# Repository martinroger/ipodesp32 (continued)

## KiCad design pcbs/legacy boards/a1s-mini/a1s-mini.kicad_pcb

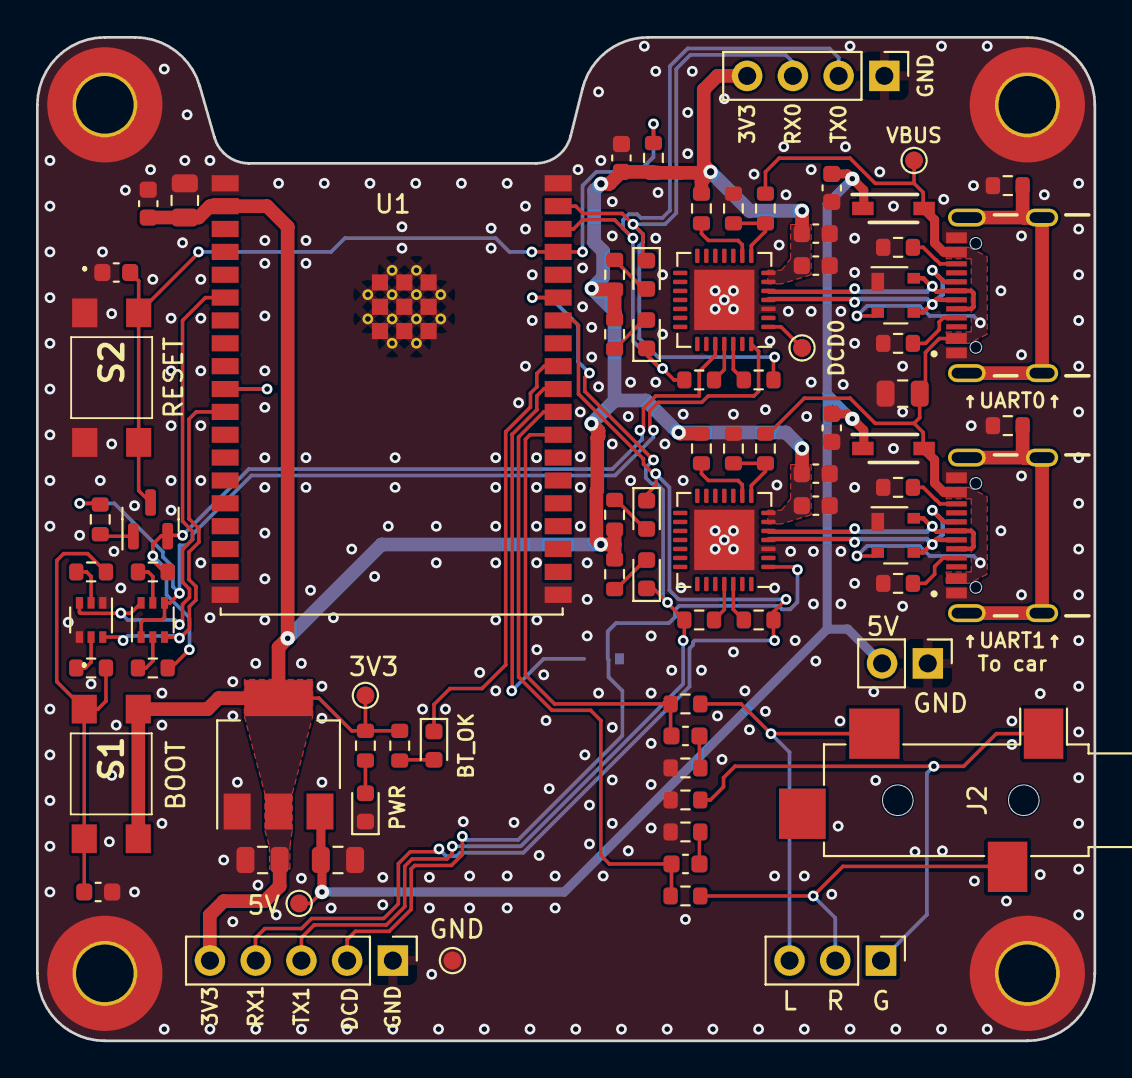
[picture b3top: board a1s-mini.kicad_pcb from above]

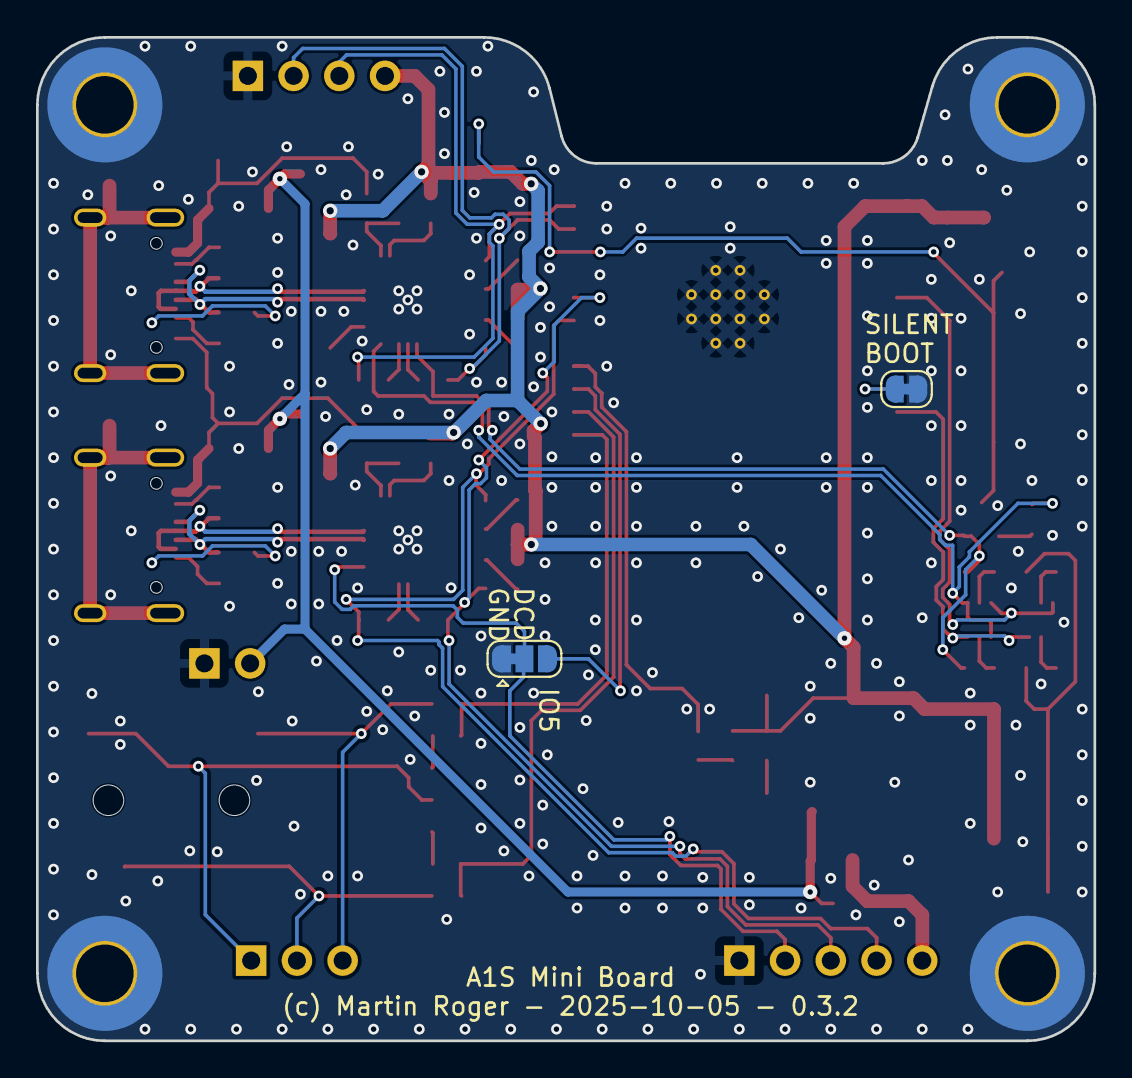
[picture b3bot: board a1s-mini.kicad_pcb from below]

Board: 2 copper layers, 58.8 x 55.7 mm, 86 parts (2 on the bottom side), 55 nets.

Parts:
3V1, 5V1: TestPoint_Small; TestPoint_Pad_D1.0mm
C1, C3, C4, C5, C8, C9, C11, C14: 0.1uF 50V; C_0603_1608Metric
C2, C6, C7, C16: 22uF 10V; C_0805_2012Metric
C10, C12, C13, C15: 10uF 10V; C_0603_1608Metric
D1, D2, D9, D11: 2.1V G 10mA; LED_0603_1608Metric
D5: 2.1V O 10mA; LED_0603_1608Metric
D6: 2V R 10mA; LED_0603_1608Metric
D7, D8: SP0503BAHTG; SOT-143
D10, D14: 1N5819HW-7-F; SOD3716X145N
DCD1: TestPoint_Small; TestPoint_Pad_D1.0mm
GND1: TestPoint_Small; TestPoint_Pad_D1.0mm
H1, H2, H3, H4: MountingHole_Pad; MountingHole_3.2mm_M3_Pad_TopBottom
J1: UART1; PinHeader_1x05_P2.54mm_Vertical
J2: SJ-3524-SMT-TR-PI; Jack_3.5mm_CUI_SJ-3524-SMT_Horizontal
J3: Audio Out; PinHeader_1x03_P2.54mm_Vertical
J4: UART0; PinHeader_1x04_P2.54mm_Vertical
J5, J6: USB4105-GF-A; GCT_USB4105-GF-A
J7: 5V; PinHeader_1x02_P2.54mm_Vertical
JP1: SolderJumper_3_Bridged12; SolderJumper-3_P1.3mm_Bridged12_RoundedPad1.0x1.5mm
JP2: SolderJumper_2_Bridged; SolderJumper-2_P1.3mm_Bridged_RoundedPad1.0x1.5mm
Q3: BC818; SOT-23
Q4, Q6: MBT3904DW1; SOT-363_SC-70-6
R1, R2, R5, R6, R34, R35: 1K 1%; R_0603_1608Metric
R7, R12, R13, R14, R32, R33: 10K 1%; R_0603_1608Metric
R8, R9: 22R 1%; R_0603_1608Metric
R10, R11, R18, R19, R21, R26, R27, R29, R31: 0R; R_0603_1608Metric
R15, R23: 22.1K 1%; R_0603_1608Metric
R16, R24: 47.5K 1%; R_0603_1608Metric
R17, R25: 2K 1%; R_0603_1608Metric
R20, R22, R28, R30: 5.1K 1%; R_0603_1608Metric
S1, S2: TL3305BF260QG
U1: ESP32 A1S; ESP32-A1S
U2: AZ1117CH-3.3TRG1; SOT-223-3_TabPin2
U3: CP2102N; QFN-28-1EP_5x5mm_P0.5mm_EP3.35x3.35mm
U4: CP2102-GM; QFN-28-1EP_5x5mm_P0.5mm_EP3.35x3.35mm
VBUS1: TestPoint_Small; TestPoint_Pad_D1.0mm

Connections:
+3.3V: 3V1.1, C1.2, C2.2, C3.2, C7.2, C10.2, C11.2, C13.2, C14.2, J1.5, J4.4, R1.1, R2.1, R5.1, R6.1, R7.1, R17.1, R25.1, R34.1, R35.1, S1.3, S1.4, U1.2 (3V3), U2.2 (VO), U3.6 (VDD), U3.7 (VREGIN), U4.6 (VDD), U4.7 (VREGIN)
+5V: 5V1.1, C6.2, C12.2, C15.2, D10.1, D14.1, J7.2, U2.3 (VI)
/CP2102N_0/D+: D7.3 (K), J5.A6 (DP1), J5.B6 (DP2), U3.4 (D+)
/CP2102N_0/D-: D7.4 (K), J5.A7 (DN1), J5.B7 (DN2), U3.5 (D-)
/CP2102N_0/DCD: DCD1.1, U3.1 (~DCD)
/CP2102_1/D+: D8.3 (K), J6.A6 (DP1), J6.B6 (DP2), U4.4 (D+)
/CP2102_1/D-: D8.4 (K), J6.A7 (DN1), J6.B7 (DN2), U4.5 (D-)
/CP2102_1/DCD: J1.2, JP1.2 (C), U4.1 (~DCD)
AGND: J2.S, J3.1, R31.1
DTR0: Q6.1 (E1), Q6.4 (E2), R12.1, U3.28 (~DTR)
EN: C8.2, Q3.3 (C), R7.2, S2.3, S2.4, U1.35 (EN)
GND: C1.1, C2.1, C3.1, C6.1, C7.1, C8.1, C9.1, C10.1, C11.1, C12.1, C13.1, C14.1, C15.1, C16.1, D5.1 (K), D7.1 (A), D8.1 (A), GND1.1, H1.1, H2.1, H3.1, H4.1, J1.1, J4.1, J5.A1_B12 (GND), J5.B1_A12 (GND__1), J6.A1_B12 (GND), J6.B1_A12 (GND__1), J7.1, JP1.1 (A), JP2.2 (B), Q4.1 (E1), Q4.4 (E2), R8.2, R9.2, R16.2, R20.1, R21.2, R22.2, R24.2, R28.1, R29.2, R30.2, R31.2, S2.1, S2.2, U1.1 (GND), U1.19 (GND), U1.20 (GND), U1.38 (GND), U1.39 (GND), U2.1 (GND), U3.3 (GND), U3.29 (GND), U4.3 (GND), U4.29 (GND)
HPOUTL: C4.2, R10.1, U1.27 (HPOUTL)
HPOUTR: C5.2, R11.1, U1.28 (HPOUTR)
IO0: Q4.3 (C2), Q6.6 (C1), U1.6 (IO0)
IO2: Q4.6 (C1), Q6.3 (C2), U1.11 (IO2)
IO5: JP1.3 (B), U1.29 (IO5)
IO18: D6.1 (K), U1.30 (IO18)
LOUT: J2.T, J3.3, R10.2
unnamed: C4.1, R8.1
unnamed: C5.1, R9.1
unnamed: C9.2, R32.1, R33.1, S1.1, S1.2
unnamed: D1.2 (A), R1.2
unnamed: D2.2 (A), R2.2
unnamed: D5.2 (A), R5.2
unnamed: D6.2 (A), R6.2
unnamed: D9.2 (A), R34.2
unnamed: D11.2 (A), R35.2
unnamed: J5.A5 (CC1), R20.2
unnamed: J5.B5 (CC2), R22.1
unnamed: J5.SH1 (SHELL_GND), J5.SH2 (SHELL_GND__1), J5.SH3 (SHELL_GND__2), J5.SH4 (SHELL_GND__3), R21.1
unnamed: J6.A5 (CC1), R28.2
unnamed: J6.B5 (CC2), R30.1
unnamed: J6.SH1 (SHELL_GND), J6.SH2 (SHELL_GND__1), J6.SH3 (SHELL_GND__2), J6.SH4 (SHELL_GND__3), R29.1
unnamed: JP2.1 (A), U1.10 (IO15)
unnamed: Q3.1 (B), R12.2
unnamed: Q4.2 (B1), R33.2
unnamed: Q4.5 (B2), R32.2
unnamed: Q6.2 (B1), R13.2
unnamed: Q6.5 (B2), R14.2
unnamed: R19.1, U3.25 (RXD)
unnamed: R18.1, U3.26 (TXD)
unnamed: R15.2, R16.1, U3.8 (VBUS)
unnamed: R17.2, U3.9 (~RST)
unnamed: R27.1, U4.25 (RXD)
unnamed: R26.1, U4.26 (TXD)
unnamed: R23.2, R24.1, U4.8 (VBUS)
unnamed: R25.2, U4.9 (~RST)
ROUT: J2.R, J3.2, R11.2
RTS0: Q3.2 (E), R13.1, R14.1, U3.24 (~RTS)
RXD0: D1.1 (K), J4.3, R18.2, U1.37 (RXD0)
RXD1: D9.1 (K), J1.4, R26.2, U1.32 (IO19)
TXD0: D2.1 (K), J4.2, R19.2, U1.36 (TXD0)
TXD1: D11.1 (K), J1.3, R27.2, U1.33 (IO22)
VBUS: C16.2, D7.2 (K), D8.2 (K), D10.2, D14.2, J5.A4_B9 (VBUS), J5.B4_A9 (VBUS__1), J6.A4_B9 (VBUS), J6.B4_A9 (VBUS__1), R15.1, R23.1, VBUS1.1

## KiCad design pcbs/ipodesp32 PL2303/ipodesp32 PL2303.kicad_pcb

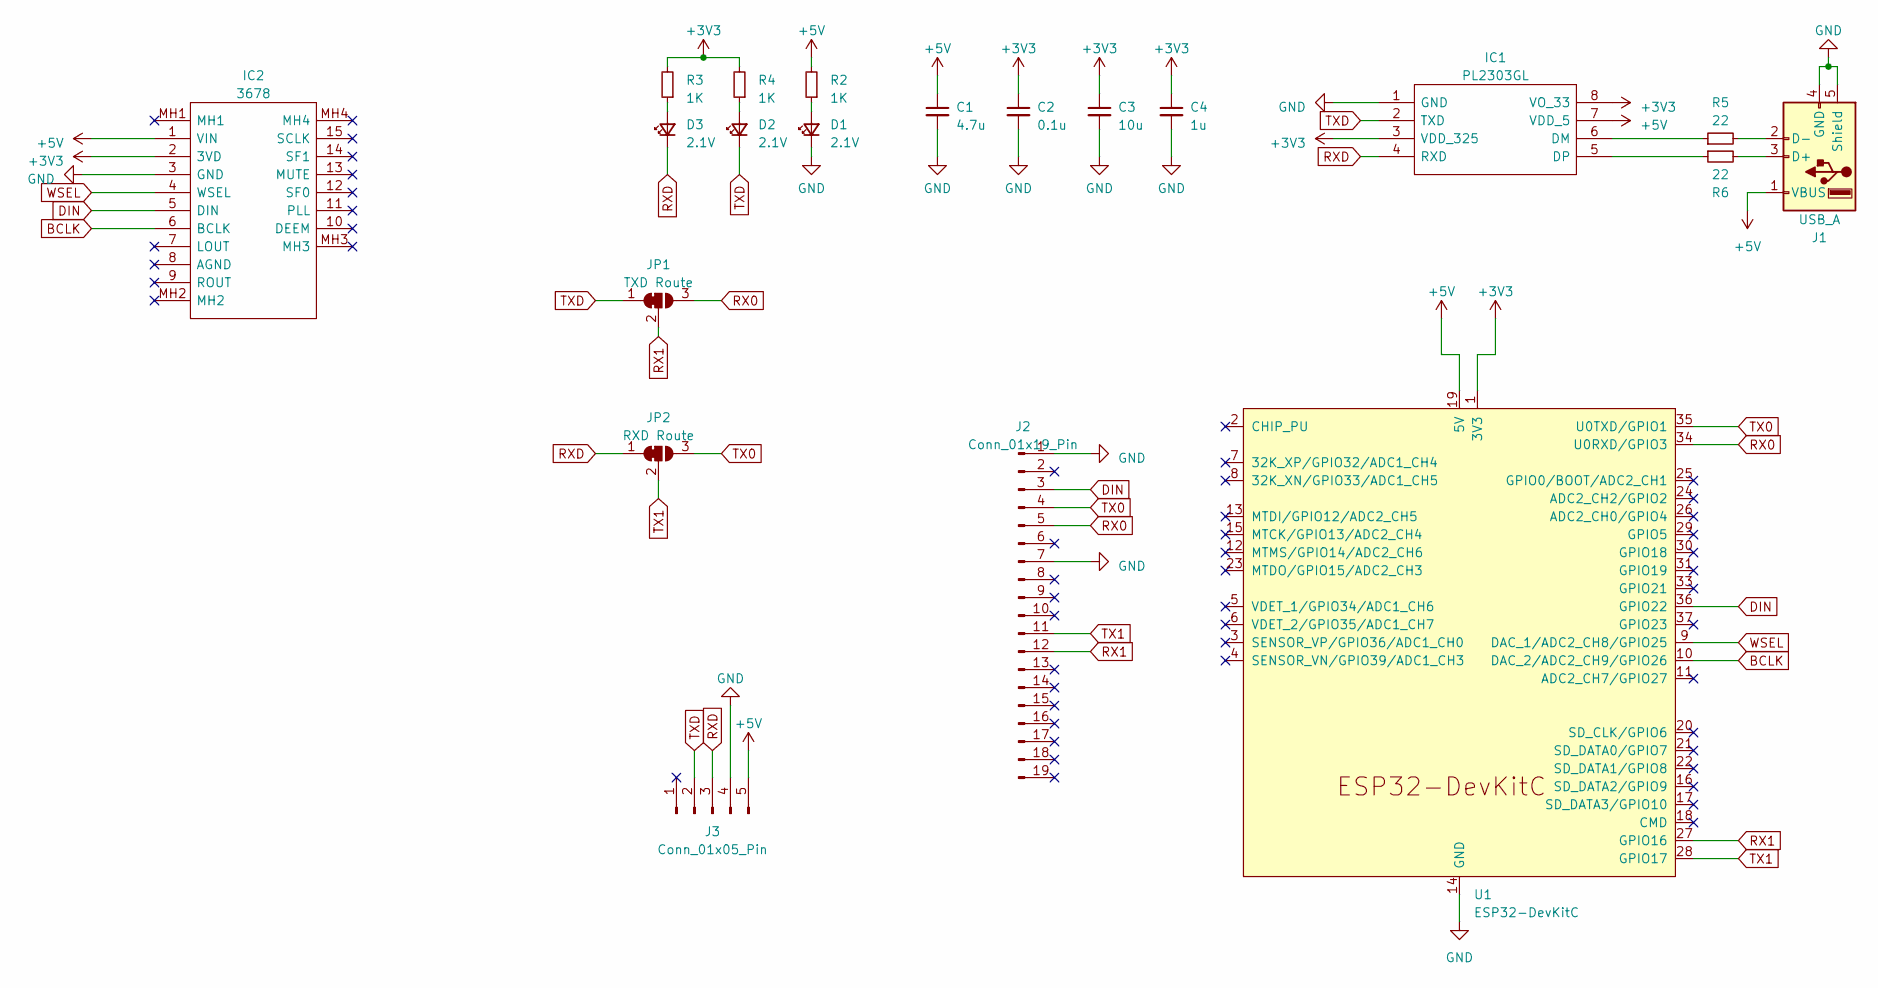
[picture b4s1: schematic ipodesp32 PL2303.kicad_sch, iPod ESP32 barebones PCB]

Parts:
C1: 4.7u; C_0603_1608Metric; Manufacturer_Part_Number CL10A475KP8NNNC
C2: 0.1u; C_0603_1608Metric; Manufacturer_Part_Number CC0603KRX7R7BB104
C3: 10u; C_0805_2012Metric; Manufacturer_Part_Number C0805C106K8PAC7800
C4: 1u; C_0603_1608Metric; Manufacturer_Part_Number CL10B105KP8NNNC
D1, D2, D3: 2.1V; LED_0603_1608Metric; Manufacturer_Part_Number LTST-C190GKT
IC1: PL2303GL; SOIC127P600X170-8N; Manufacturer_Part_Number PL2303GS
IC2: 3678; Manufacturer_Part_Number 3678
J1: USB_A; USB_A_CNCTech_1001-011-01101_Horizontal; Manufacturer_Part_Number 1001-011-01101
J2: Conn_01x19_Pin; PinHeader_1x19_P2.54mm_Vertical
J3: Conn_01x05_Pin; PinHeader_1x05_P2.54mm_Vertical
JP1: TXD Route; SolderJumper-3_P1.3mm_Bridged12_Pad1.0x1.5mm
JP2: RXD Route; SolderJumper-3_P1.3mm_Bridged12_Pad1.0x1.5mm
R2, R3, R4: 1K; R_0603_1608Metric; Manufacturer_Part_Number RC0603FR-071KL
R5, R6: 22; R_0603_1608Metric; Manufacturer_Part_Number RC0603FR-0722RL
U1: ESP32-DevKitC

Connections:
+3V3: C2.1, C3.1, C4.1, IC1.3 (VDD_325), IC1.8 (VO_33), IC2.2 (3VD), R3.2, R4.2, U1.1 (3V3)
+5V: C1.1, IC1.7 (VDD_5), IC2.1 (VIN), J1.1 (VBUS), J3.5, R2.2, U1.19 (5V)
BCLK: IC2.6 (BCLK), U1.10 (DAC_2/ADC2_CH9/GPIO26)
DIN: IC2.5 (DIN), J2.3, U1.36 (GPIO22)
GND: C1.2, C2.2, C3.2, C4.2, D1.1 (K), IC1.1 (GND), IC2.3 (GND), J1.4 (GND), J1.5 (Shield), J2.1, J2.7, J3.4, U1.14 (GND), U1.32 (GND), U1.38 (GND)
unnamed: D1.2 (A), R2.1
unnamed: D2.2 (A), R4.1
unnamed: D3.2 (A), R3.1
unnamed: IC1.6 (DM), R5.1
unnamed: IC1.5 (DP), R6.1
unnamed: J1.3 (D+), R6.2
unnamed: J1.2 (D-), R5.2
RX0: J2.5, JP1.3 (B), U1.34 (U0RXD/GPIO3)
RX1: J2.12, JP1.2 (C), U1.27 (GPIO16)
RXD: D3.1 (K), IC1.4 (RXD), J3.3, JP2.1 (A)
TX0: J2.4, JP2.3 (B), U1.35 (U0TXD/GPIO1)
TX1: J2.11, JP2.2 (C), U1.28 (GPIO17)
TXD: D2.1 (K), IC1.2 (TXD), J3.2, JP1.1 (A)
WSEL: IC2.4 (WSEL), U1.9 (DAC_1/ADC2_CH8/GPIO25)

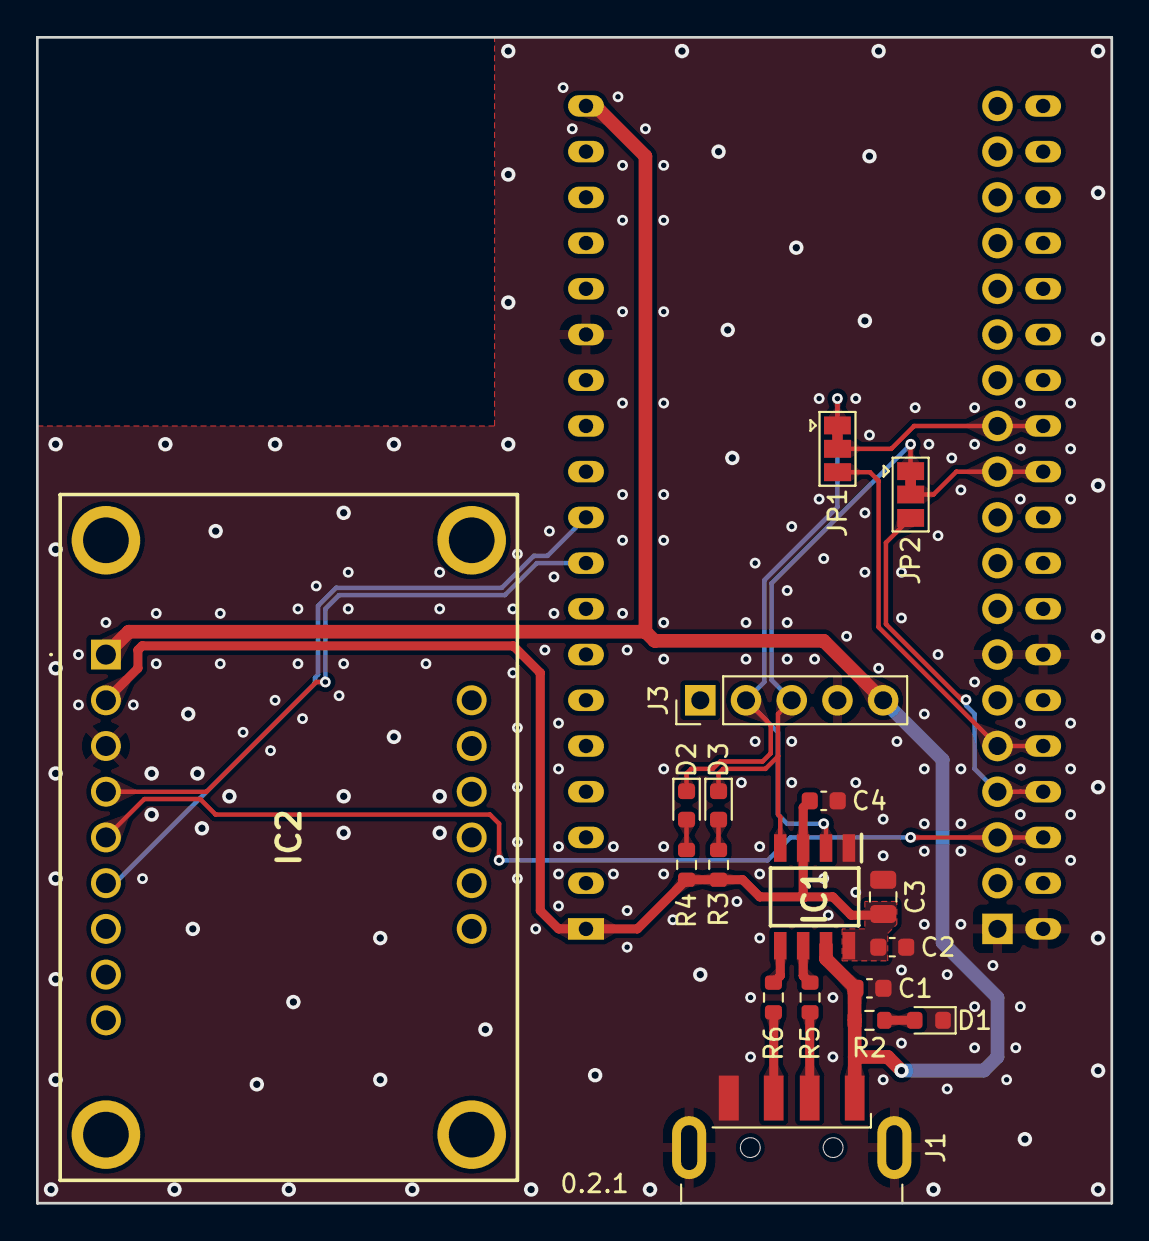
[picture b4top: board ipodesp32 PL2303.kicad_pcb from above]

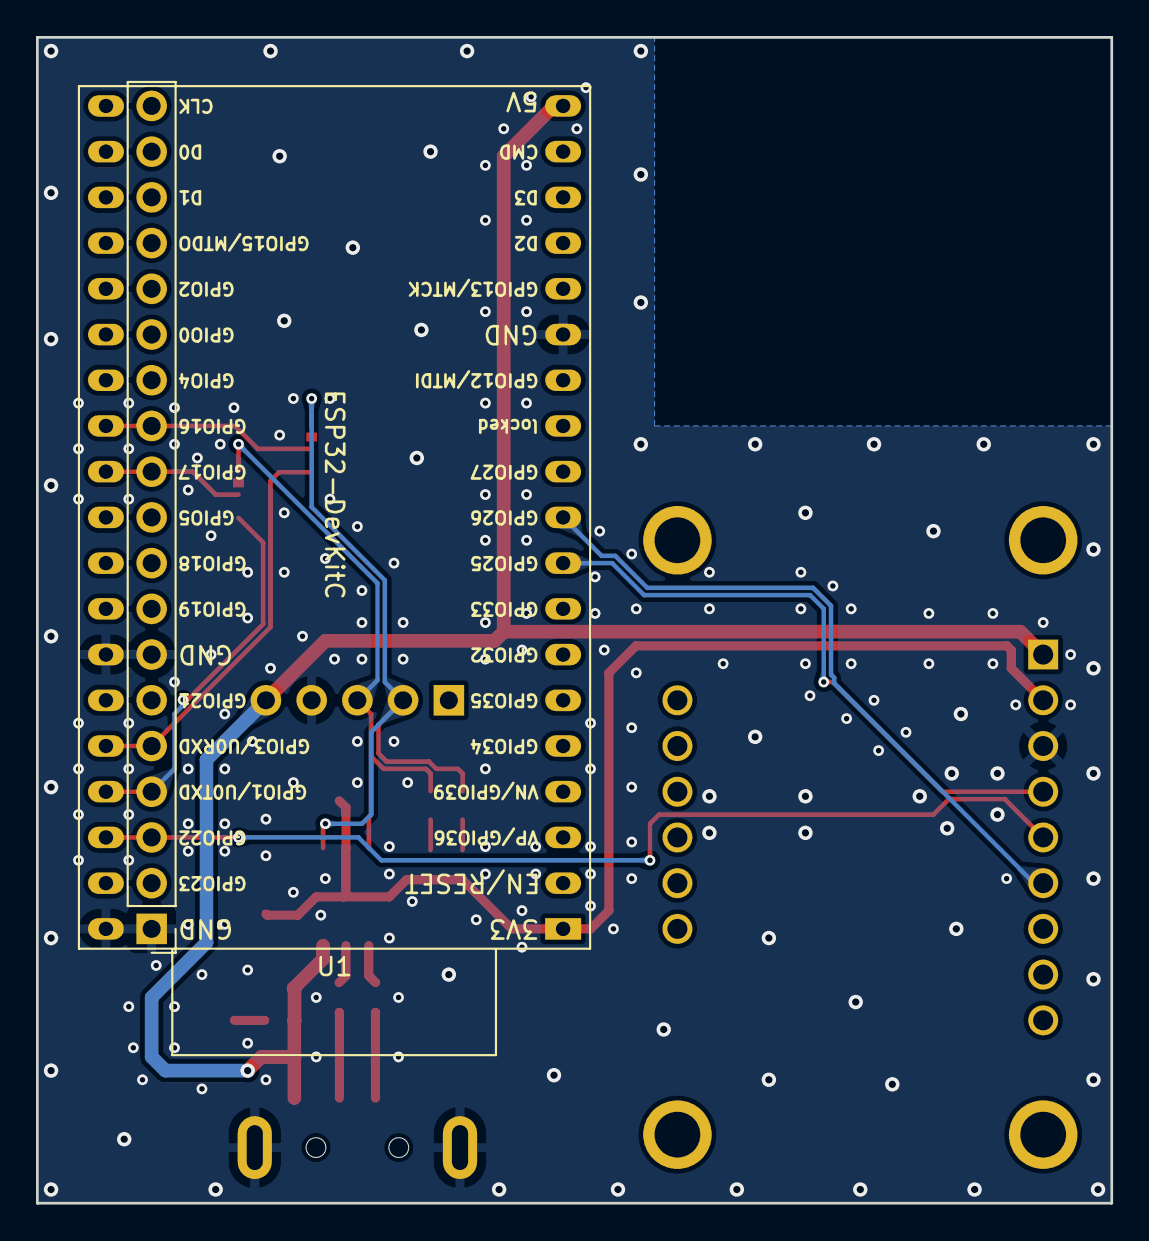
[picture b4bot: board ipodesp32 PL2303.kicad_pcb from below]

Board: 2 copper layers, 59.7 x 64.8 mm, 20 parts (2 on the bottom side), 19 nets.

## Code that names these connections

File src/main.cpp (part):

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#define INVERT_DCD_LOGIC(stateBoolean) !stateBoolean
#endif

// DCD control pin to pretend there is a physical disconnect
#if defined(ENABLE_ACTIVE_DCD) && !defined(DCD_CTRL_PIN)
#define DCD_CTRL_PIN 5
#endif
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#ifndef WS_PIN
#define WS_PIN 25
#endif
#ifndef DIN_PIN
#define DIN_PIN 26
#endif
#ifndef BCLK_PIN
#define BCLK_PIN 27
#endif

#ifdef AUDIOKIT // Using the AiThink A1S AudioKit chip
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{
#ifdef AUDIOKIT
	minimalPins.addI2C(PinFunction::CODEC, 32, 33);
	minimalPins.addI2S(PinFunction::CODEC, 0, BCLK_PIN, WS_PIN, DIN_PIN, 35);
	// a2dp_sink.set_stream_reader(read_data_stream, false); // Might need commenting out
	auto cfg = i2s.defaultConfig();
	cfg.copyFrom(info);
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	a2dp_sink.set_stream_reader(read_data_stream, false);
	auto cfg = i2s.defaultConfig(TX_MODE);
	cfg.pin_ws = WS_PIN;
	cfg.pin_data = DIN_PIN;
	cfg.pin_bck = BCLK_PIN;
	cfg.sample_rate = 44100;
	cfg.i2s_format = I2S_LSB_FORMAT;
	i2s.begin(cfg);
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
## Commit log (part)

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2024-02-21 AVRC but no playpos
2024-04-30 IAP Supporting documentation
2024-05-12 esPod class first introduction, no A2DP
2024-05-12 Start on Lingo 0x00
2024-05-14 EnterExtendedInterfaceMode
2024-05-15 Pending ack implemented, still need to find how to return name
2024-05-17 Somehow got the ipodname req to work
2024-05-17 L0x00 Reauest ipod serial num
2024-05-18 L0x04 000C implemented (lazily)
2024-05-19 Added playStatusHandler
2024-05-19 Started merging with A2DP_sink
2024-05-19 Something not write with the names parsing
2024-05-20 External DAC for NodeMCU
    Also added the default pins for ESP32
2024-05-21 Missing instruction and some corrections
2024-05-22 Sync playstatus, additional CBs
    A bit clunky, but let's see if it works.
2024-05-24 Flourishing additional title requests on commands
    Might be unecessary in the end.
2024-05-24 Serial buffer resizing corrections
    Cause I can't read the manual, visibly
2024-05-25 Fetching track duration
2024-05-25 Update for external DAC, size still too big
2024-05-25 board_build.partitions = huge_app.csv
2024-05-27 Corrections, additional enum
2024-05-27 Repaired tabbing
2024-05-27 Formatting and some overloading
    Doxygen start !
    Overload on L0x00_0x02_iPodAck
2024-05-28 Sandbox commit
2024-05-29 Up to line 943
2024-05-31 Default and auto reconnect
2024-05-31 Formatting
2024-05-31 Readme + images
2024-06-03 PL2303 board release
2024-06-04 Update to PCB with integrated PL2303
2024-07-09 Serial and PCBWay bom
2024-07-09 Return of Serial 2
2024-07-16 Corrected GS to GL on PL2303
2024-08-27 Update main.cpp
    resetState before bluetooth disable.
2024-08-28 Added previous metadata and index tracker
    Capability to compare to the previous set of metadata and previous trackIndex
2024-08-28 Update esPod.cpp
    Edge case of the first track to play and making sure that metadata is pulled in.
2024-09-03 Update main.cpp
    Start of reshape of metadata callback
2024-09-04 Update main.cpp
    Remove unused char array
2024-09-12 Metadata spaghetti
2024-09-12 DEBUG_MODE insertions
    Adding some DEBUG_MODE snippets
2024-09-13 Clean-up and debug complete
    - TrackDuration integrated to metadata despamming and management
    - removal of unused properties from espod class
    - Refactoring and realigning of PB Control on the index-based track change lingo commands
    - Removal of all mentions to DEBUG_MODE and DUMP_MODE in Packet Disneyland
2024-09-14 Bug Correction #7
    Hazardous tempTrackIndex called in PlayControl led to loop situations.
    Attempt to fix #7
    Still need to figure out if it is sending Prev or Previous Track to rewind over PlayControl
2024-09-14 Update platformio.ini
    Adding release anchor configuration
2024-09-16 Update esPod.cpp
    PlayStatus accidentally killed to stopped because of a missing equal sign.
2024-09-18 Experimental pre-alloc removal
2024-09-19 Images
2024-10-24 Core debug level increase in DEBUG_MODE
2024-11-08 Reverting to 5ms intervql
2024-11-15 Connection LED, reassigned to UART0
2024-11-18 Header segregation
2024-11-18 SD Card update base implementation
2024-11-18 ESP_LOGE example
2024-11-18 Small changes
2024-11-19 Restart from there
2024-11-26 Removing TAG shields
2024-11-26 Baud and log level adjustment for certainty
2024-11-26 Update platformio.ini
    Locking in the libdep versions
2024-11-27 Update main.cpp
    ESP_LOGI inserts in main file
2024-11-28 Update esPod.cpp
    Lingo 0 and Lingo 4 functions done. Lingo processors next.
2024-11-29 Pruning DEBUG_MODE entries
2024-11-30 Finding the board definition conflicts with SDMMC
2024-11-30 Clean-up
2024-12-02 SingleShot send function
2024-12-04 Multi troublefinding configs
    Related to the steps in #16
2024-12-05 Branch information in the debug messages
2024-12-07 Break between RX strings
2024-12-07 Initial implementation of 500ms notifications
2024-12-15 Double flag handshake implementation
2025-01-07 Update platformio.ini
    Strict version pointing
2025-01-07 Update platformio.ini
    Thank you @pschatzmann !!
    Fixed issues with incoming mutex in Audio-Tools
2025-01-22 Base setup
2025-02-02 RX Task and basic utilities
    - Added aapCommand structure : pointer to a payload buffer, and uint32_t length member
    - Defined SERIAL_TIMEOUT and INTERBYTE_TIMEOUT for pulling out of unfinished packets or dropped bytes -> Still requires NAck return if a packet has been started.
    - Defined two FreeRTOS queues : cmdQueue for RX commands to be processed, _txQueue for messages to be transmitted back to the accessory
    - Defined three tasks : _rxTask for processing incoming Serial at low priority, _processTask to advise actions and send back to the _txQueue
    - Completed _rxTask writeup
    - Some comfortable macros added to espod.h
2025-02-03 Small cleanup
    - Making sure private methods are prefixed with an underscore
    - Review before trying to queue metadata for offset processing
2025-02-03 Correction
2025-02-03 TrackChangeAckPending management
    TrackChangeAckPending cancellation is handled either by sending another ack for the same command directly, or when it is called in the timer callback
2025-02-03 Moving AVRC Metadata processing to low prio task
    AVRC callback is short (memory allocation), now introducing processAVRCTask for async processing !
2025-02-03 AVRC Macros, HWM logging in Main
    - Macros for the AVRC process task stack/priority/queue control
    - Optional HWM logging of AVRC process stack in main.
2025-02-04 Stack size update
2025-02-04 Interval relaxation
2025-02-05 xQueueFromISR, separate timer queue (copiloted)
2025-02-06 Pause before _tx actual packet sending
2025-02-06 Firmware.cur introduction
    Keep traceability of the older FW
2025-02-06 Formatting part 2
2025-02-07 Logging load adjustments
2025-02-07 Externalising rxIncomplete
    Semaphore-free attempt at making sure that as long as _rxTask is not done receiving a complete packet, _txTask should jump wait
2025-02-08 Less incomplete packets, to test on car
2025-02-09 Missed first shake of hand patch
    Correcting the case where the mini doesn't receive the first request capability and fails to start the handshake.
2025-02-10 Corrections and AVRC Macro
2025-02-15 HeartBeat timer introduction
2025-02-16 Sandwich
2025-02-17 Reset reason + Reassignment on ESP_LOGI tags
2025-02-17 Code and options reduction
    Less build options
    De-cluttering of main.cpp
2025-02-17 Formatting and processor directives simplification
2025-02-17 Reformat of esPod class
2025-02-19 Simplified footprints, schematic revisited
2025-02-20 Pause TX on pending, jump Queue for Ack
    - Inhibits TX-ing until one of the Acks has hit
    - Moves the Ack message at the front of the queue to avoid issues of interstitial message received in meantime
2025-02-20 Format with C C++
2025-02-21 Adds multiple lines of version info before building
2025-02-23 Starting A1S Mini, teardrops on sandwhich
2025-02-24 Progress on differential routing
2025-02-26 Timeout reduction, small correction
    Timeout reduced to 2500ms
    Logging message correction
    v0.4.3
2025-02-26 Restart A1S mini
2025-02-27 Outline
2025-03-01 A1S Mini quote PCBWay
2025-03-01 Corrections to Serial and Pin
    - Stop using Serial2 and reallocate UART1 for devkit based solution
    - Still some issues with stream write ? Need to use callback ?
2025-03-01 Sandwich board adjustments
2025-03-03 Haut de forme v0.1
2025-03-03 3D checks
2025-03-06 Images added
2025-03-11 Projects consistency update
2025-03-18 Update SCB
    Updated SCB :
    - Upper pins of CP2104 moved about 0.5mm up
    - CP2104 reset is now available on GPIO 13
2025-03-19 Adding bulk 5V capacitor to SCB
2025-03-21 libdep check and readme update
2025-03-30 A1S mini corrected, v0.3.0
2025-04-06 Adding LED_BUILTIN support for connection state
2025-04-17 PCM5102A implementation (initial schematics)
2025-05-15 Platformio.ini correction
2025-05-20 A1S Mini addition to platformio
    First A1S Mini assembled and added to platformio
2025-05-21 Adding CP2102N configs
2025-05-22 Extending debug and forcing handshake
    - Polling for extended interface mode promoted to LOGI
    - Request protocol version on L0x04 also now triggers a handshake chain with the head unit... hopefully
    - Serial timeout increased from 2500ms to 60000ms
2025-05-22 Pre-layout
2025-05-23 Adding analogReadMillivolts to the snooper
2025-05-24 Loose bytes warning message in rxTask
    - Added a loose byte warning message when not receiving starter bytes on RX (might spam the console)
    - Parenthesis escaping for Unix compatibility in platformio.ini
2025-05-25 Support for L0x00_0x24
    Adding support for GetiPodOptions command, plus a few other things.
2025-05-26 Move to CP2102 non N
2025-05-26 Big mergy merge
2025-05-26 Bringing up iPod instance name in esPod_conf
2025-05-27 Finding the limit
    Accelerating communication after the squash-merge
2025-06-02 PCB updates
2025-06-03 Reinstating L0x00_0x27 spamming
    Looks like it works OK ?
2025-06-04 Platformio Linux compatibility fix
2025-06-04 Task control and major refactor (#40)
    * Update platformio.ini
    * Update platformio.ini
    * Clean-up and audioKit.json
    * RX Task and basic utilities
    - Added aapCommand structure : pointer to a payload buffer, and uint32_t length member
    - Defined SERIAL_TIMEOUT and INTERBYTE_TIMEOUT for pulling out of unfinished packets or dropped bytes -> Still requires NAck return if a packet has been started.
2025-06-04 Clean up of PCB and schematic
2025-06-06 Corrections
2025-06-07 Pre-implementation L0x03
2025-06-08 Lingo 0x03 Overhaul
2025-06-09 Lingo fixes for 0x00 and 0x04
    Lingo 0x00 :
    - RetiPodOptions correction of the options bit field
    Lingo 0x04 :
    - Adding functions for returning screen limits for displaying images. In theory should not be queried but the RetiPodOptions was bodged...
    - Enabled L0x04_SelectSortDBRecord, even though it does nothing interesting.
    - Added two categories responses with "--" for podcasts and audiobooks for cmd 0x001A. Previously would return complaining iPodAck.
2025-07-19 bt modularize: attempt 2
2025-08-31 Adding equivalent JLCPCB values
2025-09-01 JLCPCB Order v0.1.6
2025-09-23 Updating libs and platfor;
2025-09-28 Update platformio.ini
    Moving to :
    - ESP32-A2DP v1.8.8
    - Arduino audio tools 1.2.0
    Compiles fine, not checked for working order
2025-10-05 Build config update
2025-10-05 UART0 LEDs correction
2025-10-05 STEP file reference
2025-10-21 CP2104 layout
2025-10-22 A1S updated to CP2104
    Version numbers also updated
2026-01-18 Update README with CP2102 chip caveats and solution
    Added a warning about CP2102 chip compatibility and mentioned a potential solution using ESP32S3.
2026-02-15 Class architecture update
2026-02-17 Simplification
2026-02-17 External esPod library
2026-02-19 Preliminary S3 version schematic and layout
2026-02-20 Local library testing configs
2026-02-20 Refactor GitHub Actions workflow for PlatformIO
2026-02-20 Update pull request types in workflow configuration
2026-02-22 PlatformIO alignment before PR
2026-02-22 Resolves hazardous metadata reception
2026-02-22 Update to latest core and libdep
